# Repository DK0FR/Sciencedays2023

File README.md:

# Sciencedays2023

Project files for the Sciencedays 2023 Project: PCB Coil BLDC Motor.

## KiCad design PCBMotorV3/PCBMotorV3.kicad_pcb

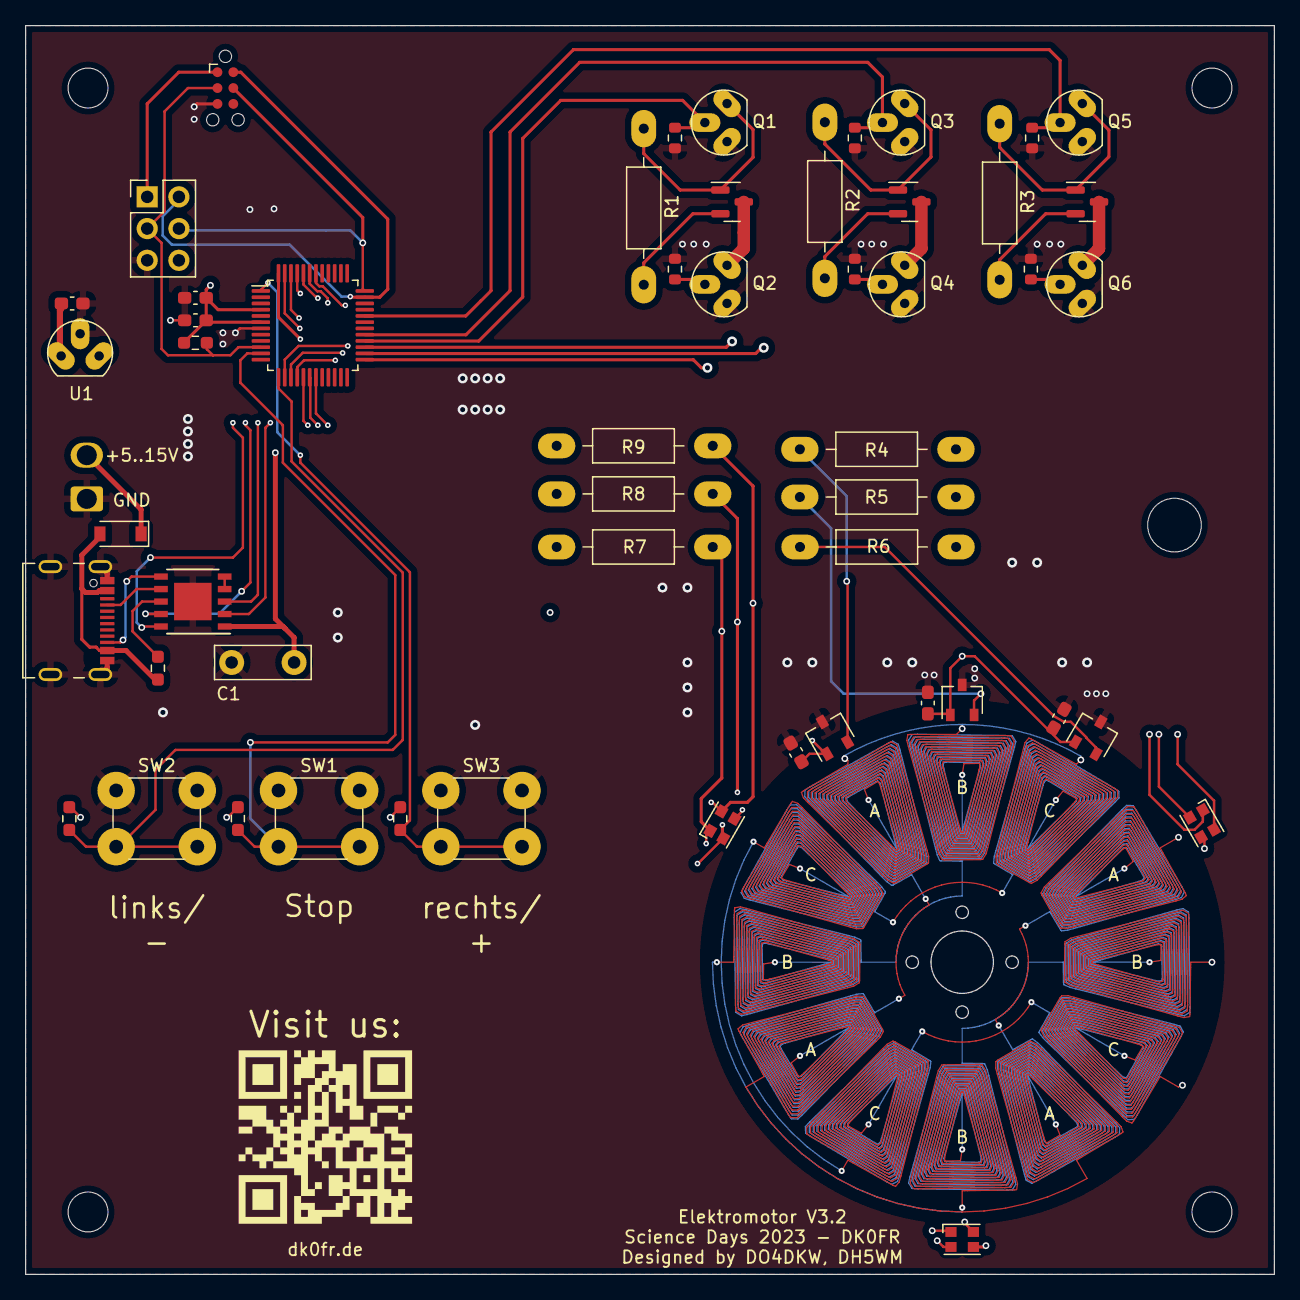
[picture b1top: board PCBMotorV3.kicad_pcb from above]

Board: 4 copper layers, 100.0 x 100.0 mm, 58 parts (0 on the bottom side), 40 nets.

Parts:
C1: 1u; C_Disc_D7.5mm_W2.5mm_P5.00mm
C6, C8, C10, C11, C12, C50: 100n; C_0603_1608Metric_Pad1.08x0.95mm_HandSolder
D1, D2, D3: LED_RGBA; LED_ASMB-KTF0-0A306
D4: D; D_SOD-123
H1, H2, H3, H4: MountingHole; MountingHole_3.2mm_M3
H5: MountingHole; MountingHole_4.3mm_M4
J1: Conn_01x02; 2Pol_THT
J2: C2927293; USB_C_C2927293
J3: Conn_ARM_SWD_TagConnect_TC2030; Tag-Connect_TC2030-IDC-NL_2x03_P1.27mm_Vertical
Q1, Q2, Q3, Q4, Q5, Q6: 2N7000; TO-92
Q10, Q11, Q13: AO3401A; SOT-23
R1, R2, R3: 10k; R_Axial_DIN0207_L6.3mm_D2.5mm_P12.5mm_Horizontal
R4, R5, R6: 5.1k; R_Axial_DIN0207_L6.3mm_D2.5mm_P12.5mm_Horizontal
R7: 120; R_Axial_DIN0207_L6.3mm_D2.5mm_P12.5mm_Horizontal
R8: 56; R_Axial_DIN0207_L6.3mm_D2.5mm_P12.5mm_Horizontal
R9: 47; R_Axial_DIN0207_L6.3mm_D2.5mm_P12.5mm_Horizontal
R10, R11, R12, R13, R50: 10k; R_0603_1608Metric_Pad0.98x0.95mm_HandSolder
R100, R101, R102, R103, R104, R105: 10k; R_0603_1608Metric
SW1, SW2, SW3: SW_Push; SW_PUSH_6mm_H7.3mm
U1: AP7384-33V; TO-92
U2: CH224K; SSOP-10_3.9x4.9mm_P1.00mm_EP3x3mm
U3: STM32G030C8Tx; LQFP-48_7x7mm_P0.5mm
U4: DebugConn; PinHeader_2x03_P2.54mm_Vertical
U5, U6, U7: CH941SR; SOT-23W

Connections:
+3.3V: C1.2, C6.1, C8.1, C10.1, C11.1, C12.1, C50.1, J3.1 (VCC), R4.1, R5.1, R6.1, R10.1, R11.1, R12.1, R50.1, U1.1 (VO), U2.1 (VDD), U3.4 (VBAT), U3.6 (VDD), U4.1, U5.1 (VCC), U6.1 (VCC), U7.1 (VCC)
/PowerStage/Hall_U: R4.2, U3.14 (PA3), U5.2 (VOUT)
/PowerStage/Hall_V: R5.2, U3.15 (PA4), U6.2 (VOUT)
/PowerStage/Hall_W: R6.2, U3.16 (PA5), U7.2 (VOUT)
/PowerStage/U_H: Q1.2 (G), R100.2, U3.28 (PA8)
/PowerStage/U_L: Q2.2 (G), R101.2, U3.25 (PB13)
/PowerStage/V_H: Q3.2 (G), R102.2, U3.29 (PA9/NC)
/PowerStage/V_L: Q4.2 (G), R103.2, U3.26 (PB14)
/PowerStage/W_H: Q5.2 (G), R104.2, U3.32 (PA10/NC)
/PowerStage/W_L: Q6.2 (G), R105.2, U3.27 (PB15)
/coils: Q2.3 (D), Q4.3 (D), Q6.3 (D), Q10.3 (D), Q11.3 (D), Q13.3 (D)
/microcontroller/BTN_LEFT: R11.2, SW2.2, U3.13 (PA2)
/microcontroller/BTN_RIGHT: R12.2, SW3.2, U3.1 (PC13)
/microcontroller/BTN_STOP: R10.2, SW1.2, U3.11 (PA0)
/microcontroller/CFG1: U2.9 (CFG1), U3.44 (PB5)
/microcontroller/CFG2: U2.2 (CFG2), U3.42 (PB3)
/microcontroller/CFG3: U2.3 (CFG3), U3.43 (PB4)
/microcontroller/LED1: D1.3 (A), U3.17 (PA6)
/microcontroller/LED2: D2.3 (A), U3.18 (PA7)
/microcontroller/LED3: D3.3 (A), U3.19 (PB0)
/microcontroller/LED_B: R9.2, U3.48 (PB9)
/microcontroller/LED_G: R8.2, U3.47 (PB8)
/microcontroller/LED_R: R7.2, U3.46 (PB7)
/microcontroller/PG: U2.10 (PG), U3.45 (PB6)
GND: C1.1, C6.2, C8.2, C10.2, C11.2, C12.2, C50.2, J1.1, J2.A1 (GND), J2.A12 (GND), J2.B1 (GND), J2.B12 (GND), J2.S1 (SHIELD), J3.5 (GND), Q1.1 (S), Q2.1 (S), Q3.1 (S), Q4.1 (S), Q5.1 (S), Q6.1 (S), R100.1, R101.1, R102.1, R103.1, R104.1, R105.1, SW1.1, SW2.1, SW3.1, U1.2 (GND), U2.11 (GND), U3.7 (VSS), U4.5, U5.3 (GND), U6.3 (GND), U7.3 (GND)
NRST: J3.3 (~RESET), R50.2, U3.10 (NRST), U4.3
unnamed: D1.1 (RK), D2.1 (RK), D3.1 (RK), R7.1
unnamed: D1.2 (BL), D2.2 (BL), D3.2 (BL), R8.1
unnamed: D1.4 (GR), D2.4 (GR), D3.4 (GR), R9.1
unnamed: D4.2 (A), J2.A4 (VBUS), J2.A9 (VBUS), J2.B4 (VBUS), J2.B9 (VBUS), R13.1
unnamed: J2.A5 (CC1), U2.7 (CC1)
unnamed: J2.B5 (CC2), U2.6 (CC2)
unnamed: Q1.3 (D), Q10.1 (G), R1.1
unnamed: Q3.3 (D), Q11.1 (G), R2.1
unnamed: Q5.3 (D), Q13.1 (G), R3.1
unnamed: R13.2, U2.8 (VBUS)
unnamed: U2.4 (DP), U2.5 (DM)
SWCLK: J3.4 (SWCLK), U3.36 (PA14), U4.4
SWDIO: J3.2 (SWDIO), U3.35 (PA13), U4.2
VCC: D4.1 (K), J1.2, Q10.2 (S), Q11.2 (S), Q13.2 (S), R1.2, R2.2, R3.2, U1.3 (VI)

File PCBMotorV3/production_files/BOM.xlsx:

Designator | Footprint | Quantity | Value | LCSC Part #
C10, C11, C12, C50, C6, C8, C9 | 0603 | 8 | 100n | C14663
J2 | USB_C_C2927293 | 1 |  | C2927293
Q10, Q11, Q13 | SOT-23 | 3 | AO3401A | C15127
R10, R100, R101, R102, R103, R104, R105, R11, R12, R13, R50 | 0603 | 9 | 10k | C25804
U2 | SSOP-10_3.9x4.9mm_P1.00mm_EP3x3mm | 1 | CH224K | C970725
U3 | LQFP-48_7x7mm_P0.5mm | 1 | STM32G030C8Tx | C529329
U5, U6, U7 | SOT-23W | 3 | CH941SR | C455292
D1, D2, D3 | LED_ASMB-KTF0-0A306 | 3 |  | C2874116
D4 | SOD123-W | 1 | B5819W SL | C8598

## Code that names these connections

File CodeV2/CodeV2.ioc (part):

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Mcu.Name=STM32G030C(6-8)Tx
Mcu.Package=LQFP48
Mcu.UserName=STM32G030C8Tx
PA0.GPIOParameters=GPIO_PuPd,GPIO_Label
PA0.GPIO_Label=STOP
PA0.GPIO_PuPd=GPIO_PULLUP
PA0.Signal=GPIO_Input
PA10.Signal=S_TIM1_CH3
PA13.Mode=Serial_Wire
PA13.Signal=SYS_SWDIO
PA14-BOOT0.Mode=Serial_Wire
PA14-BOOT0.Signal=SYS_SWCLK
PA2.GPIOParameters=GPIO_PuPd,GPIO_Label
PA2.GPIO_Label=LEFT
PA2.GPIO_PuPd=GPIO_PULLUP
PA2.Signal=GPIO_Input
PA3.GPIOParameters=GPIO_Label
PA3.GPIO_Label=HALL_U
PA3.Signal=GPXTI3
PA4.GPIOParameters=GPIO_Label
PA4.GPIO_Label=HALL_V
PA4.Signal=GPXTI4
PA5.GPIOParameters=GPIO_Label
PA5.GPIO_Label=HALL_W
PA5.Signal=GPIO_Input
PA6.GPIOParameters=GPIO_Label
PA6.GPIO_Label=LED1
PA6.Signal=GPIO_Output
PA7.GPIOParameters=GPIO_Label
PA7.GPIO_Label=LED2
PA7.Signal=GPIO_Output
PA8.Signal=S_TIM1_CH1
PA9.Signal=S_TIM1_CH2
PB0.GPIOParameters=GPIO_Label
PB0.GPIO_Label=LED3
PB0.Signal=GPIO_Output
PB13.Mode=PWM Generation1 CH1 CH1N
PB13.Signal=TIM1_CH1N
PB14.Mode=PWM Generation2 CH2 CH2N
PB14.Signal=TIM1_CH2N
PB15.Mode=PWM Generation3 CH3 CH3N
PB15.Signal=TIM1_CH3N
PB3.GPIOParameters=GPIO_Label
PB3.GPIO_Label=CFG2
PB3.Signal=GPIO_Output
PB4.GPIOParameters=GPIO_Label
PB4.GPIO_Label=CFG3
PB4.Signal=GPIO_Output
PB5.GPIOParameters=GPIO_Label
PB5.GPIO_Label=CFG1
PB5.Signal=GPIO_Output
PB6.GPIOParameters=GPIO_PuPd,GPIO_Label
PB6.GPIO_Label=PG
PB6.GPIO_PuPd=GPIO_PULLUP
PB6.Signal=GPIO_Input
PB7.GPIOParameters=GPIO_Label
PB7.GPIO_Label=LED_R
PB7.Signal=GPIO_Output
PB8.GPIOParameters=GPIO_Label
PB8.GPIO_Label=LED_G
PB8.Signal=GPIO_Output
PB9.GPIOParameters=GPIO_Label
PB9.GPIO_Label=LED_B
PB9.Signal=GPIO_Output
PC13.GPIOParameters=GPIO_PuPd,GPIO_Label
PC13.GPIO_Label=RIGHT
PC13.GPIO_PuPd=GPIO_PULLUP
PC13.Signal=GPIO_Input
RCC.HSE_VALUE=8000000
RCC.SYSCLKFreq_VALUE=64000000
RCC.SYSCLKSource=RCC_SYSCLKSOURCE_PLLCLK
board=custom

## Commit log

2023-10-25 inital commit
